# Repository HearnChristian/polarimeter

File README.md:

# Polarimeter — Photodiode Analog Front-End

A 4-layer mixed-signal PCB that reads optical polarization by measuring the
photocurrent from a pair of photodiodes through a low-noise transimpedance
signal chain. Designed in KiCad; this repository contains the full schematic,
layout, fabrication outputs, and bill of materials.

📄 **[Full schematic (PDF)](docs/Polarimeter-schematic.pdf)** · 🖼️ [board bottom](docs/board-bottom.png)

## What it does

Light passing through a polarizing optical stage lands on two photodiodes
(`D1`, `D2`). Each diode's photocurrent is converted to a voltage by a
transimpedance amplifier (TIA), filtered, and buffered for acquisition. By
comparing the two channels, the relative polarization / intensity of the
incident beam can be recovered. The board carries its own low-noise power
regulation and a precision voltage reference so the analog measurement is clean
and ratiometric.

## Signal chain

| Stage | Part | Role |
|-------|------|------|
| Photodiodes | `D1`, `D2` (TO-5) | Convert incident light to photocurrent |
| Transimpedance amps | OPA381 (precision, low-bias TIA) | I→V conversion of diode current |
| Gain / buffer | OPA320 / OPA2320 (low-noise, R-R CMOS) | Second-stage gain and buffering |
| Precision reference | REF3425 (2.5 V) | Stable ratiometric reference for the ADC path |
| Connector | 2×24 header (`J1`) + barrel jack (`J2`) | Signal breakout and DC input |

## Power

- **LT8609** synchronous step-down buck — primary rail regulation from the DC input jack.
- **LP5912-3.3** low-noise LDO — clean 3.3 V rail for the precision analog section.
- Local decoupling throughout (0.1 µF / 1 µF / 10 µF) to keep the TIA front-end quiet.

## Board

- **4 copper layers:** `F.Cu`, `In1.Cu`, `In2.Cu`, `B.Cu`
- Surface-mount construction, 0603/0805 passives
- Gerbers and drill files included for direct fabrication

## Repository layout

```
Polarimeter.kicad_pro      KiCad project
Polarimeter.kicad_sch      Root schematic
Power.kicad_sch            Power-supply sub-sheet (hierarchical)
Polarimeter.kicad_pcb      PCB layout (4-layer)
Polarimeter.csv            Bill of materials
Gerbers for AMO/           Fabrication outputs (Gerber + Excellon drill)
docs/                      Rendered schematic PDF + 3D board images
```

## Bill of materials

The full BOM lives in [`Polarimeter.csv`](Polarimeter.csv) (designator,
footprint, quantity, value). Key actives: OPA381, OPA320/OPA2320, REF3425,
LT8609, LP5912-3.3.

## Tools

Designed in [KiCad](https://www.kicad.org/). Open `Polarimeter.kicad_pro` to
view or edit the schematic and layout.

---

*Designed by Christian Hearn, with Malik Shaaban.*

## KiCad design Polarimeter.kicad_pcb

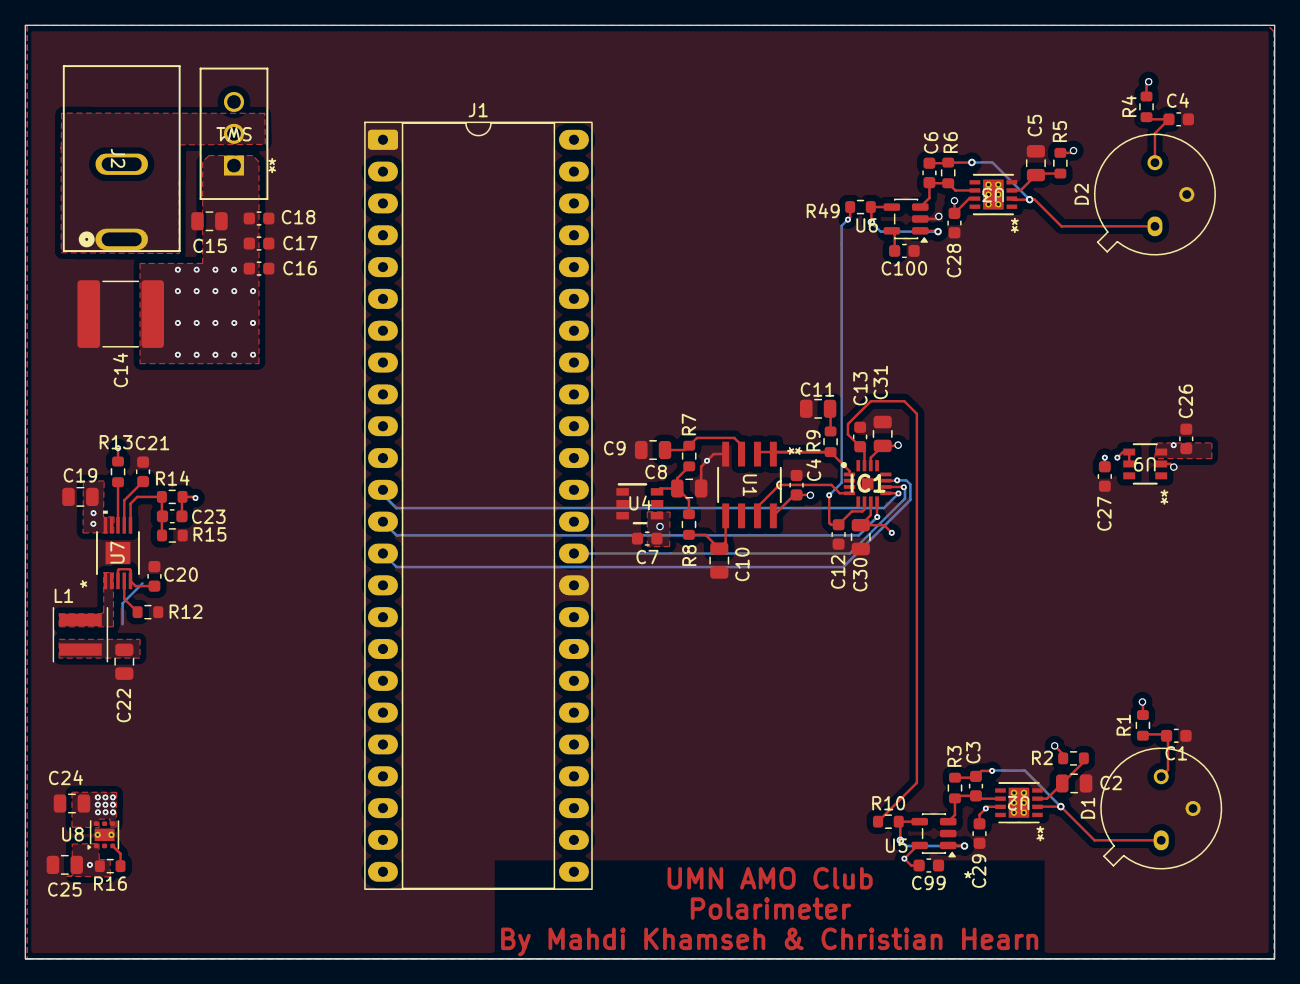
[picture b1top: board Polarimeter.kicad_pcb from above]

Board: 4 copper layers, 99.7 x 74.5 mm, 66 parts (0 on the bottom side), 34 nets.

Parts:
C1, C16, C17, C26, C27: 0.1u; C_0603_1608Metric
C2, C5: 0.1uF; C_0805_2012Metric
C3, C6: 24.7pF; C_0603_1608Metric
C4, C4#2, C28, C29, C99, C100: 0.1uF; C_0603_1608Metric
C7: 0.1 uF; C_0603_1608Metric
C8: 10uF; C_0805_2012Metric
C9, C10, C30, C31: 1 uF; C_0805_2012Metric
C11: 10 uF; C_0805_2012Metric
C12, C13: 3.3nF; C_0603_1608Metric
C14: 47u; C_2220_5750Metric
C15: 10u; C_0805_2012Metric
C18, C21: 10n; C_0603_1608Metric
C19: 4.7u; C_0805_2012Metric
C20: 1u; C_0603_1608Metric
C22: 22u; C_0805_2012Metric
C23: 10p; C_0603_1608Metric
C24: 1u; C_0805_2012Metric
C25: v; C_0805_2012Metric
D1, D2: D_Photo; TO-5-3
IC1: ADS8355IRTET; QFN50P300X300X80-17N-D
J1: Conn_02x24_Counter_Clockwise; DIP-48_W15.24mm_Socket_LongPads
J2: PJ-037AH; CONN_37AH
L1: 2.2u; L_Coilcraft_XxL4020
R1, R4, R7, R8: 1k; R_0603_1608Metric
R2, R5, R13: 100k; R_0603_1608Metric
R3, R6: 787; R_0603_1608Metric
R9: 0.1; R_0603_1608Metric
R10, R49: 49; R_0603_1608Metric
R12: 18.2 kOhms; R_0603_1608Metric
R14: 1M; R_0603_1608Metric
R15: 187k; R_0603_1608Metric
R16: 10k; R_0603_1608Metric
SW1: TS01CQE; TS01CQE_CNK
U1: OPA2320AID; D8
U2, U3: OPA381AIDRBT; DRB8_2P4X1P65
U4: REF3425IDBVR; DBV0006A_N
U5, U6: OPA320AIDBVR; SOT-23-5
U7: LT8609EMSE-TRPBF; 05-08-1664_ADI
U8: LP5912-3.3DRV; WSON-6-1EP_2x2mm_P0.65mm_EP1x1.6mm_ThermalVias
U9: ADR130AUJZ-REEL7; UJ_6_ADI

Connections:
+0.5V: C27.1, R2.1, R5.1, U9.4 (VOUT), U9.5 (SET)
+3.3V: C25.2, C26.1, C30.1, IC1.7 (DVDD), R16.2, U8.1 (OUT), U9.3 (VIN)
+5V: C4.2, C7.2, C22.2, C23.1, C24.1, C28.1, C29.1, C31.1, C99.2, C100.2, IC1.14 (AVDD), J1.48, L1.2, R13.2, R14.2, U1.8 (V+), U2.7 (V+), U3.7 (V+), U4.4 (IN), U5.5 (V+), U6.5 (V+), U8.4 (EN), U8.6 (IN)
+20V: C14.1, C15.1, C16.1, C17.1, C18.1, C19.2, R1.1, R4.1, SW1.1, U7.9 (VIN), U7.10 (EN/UV)
AINPA: C13.1, IC1.15 (AINP_A), R10.1
AINPB: C12.1, IC1.6 (AINP_B), R49.1
CS: IC1.9 (~CS), J1.12
FB: C23.2, R14.1, R15.2, U7.6 (FB)
GND: C1.1, C2.1, C4.1, C4#2.1, C5.1, C7.1, C8.2, C9.2, C10.2, C11.2, C12.2, C13.2, C14.2, C15.2, C16.2, C17.2, C18.2, C19.1, C20.1, C21.2, C22.1, C24.2, C25.1, C26.2, C27.2, C28.2, C29.2, C30.2, C31.2, C99.1, C100.1, D1.2 (A), D2.2 (A), IC1.2 (REFGND_A), IC1.3 (REFGND_B), IC1.5 (AINM_B), IC1.13 (GND), IC1.16 (AINM_A), IC1.17 (EP), J1.1, J1.34, R12.1, R15.1, U1.4 (V-), U2.4 (V-), U2.9 (EPAD), U3.4 (V-), U3.9 (EPAD), U4.1 (GND_F), U4.2 (GND_S), U4.3 (ENABLE), U5.2 (V-), U6.2 (V-), U7.11 (GND), U8.5 (GND), U8.7 (EP), U9.2 (GND)
INA+: C9.1, R7.1, U1.3 (INA+)
INB+: C10.1, R8.1, U1.5 (INB+)
INTVCC: C20.2, U7.3 (INTVCC), U7.5 (SYNC)
IN_A-: C3.2, D1.1 (K), R3.2, U2.2 (IN-)
IN_B-: C6.2, D2.1 (K), R6.2, U3.2 (IN-)
unnamed: C11.1, R9.1
unnamed: C1.2, D1.3, R1.2
unnamed: C4#2.2, D2.3, R4.2
unnamed: C2.2, R2.2, U2.3 (IN+)
unnamed: C5.2, R5.2, U3.3 (IN+)
unnamed: C8.1, R7.2, R8.2, U4.6 (OUT_F)
unnamed: R16.1, U8.3 (PG)
OUT320_A: R10.2, U5.1 (OUT), U5.4 (IN-)
OUT320_B: R49.2, U6.1 (OUT), U6.4 (IN-)
PG: R13.1, U7.8 (PG)
RT: R12.2, U7.4 (RT)
SDI: IC1.8 (SDI), J1.13
SDOA: IC1.11 (SDO_A), J1.14
SW: L1.1, U7.1 (BST), U7.2 (SW)
TR/SS: C21.1, U7.7 (TR/SS)
V OUTPUT_A: C3.1, R3.1, U2.6 (OUTPUT), U5.3 (IN+)
V OUTPUT_B: C6.1, R6.1, U3.6 (OUTPUT), U6.3 (IN+)
clk: IC1.10 (SCLK), J1.35
refA: IC1.1 (REFIO_A), R9.2, U1.1 (OUTA), U1.2 (INA-)
refB: IC1.4 (REFIO_B), U1.6 (INB-), U1.7 (OUTB)
